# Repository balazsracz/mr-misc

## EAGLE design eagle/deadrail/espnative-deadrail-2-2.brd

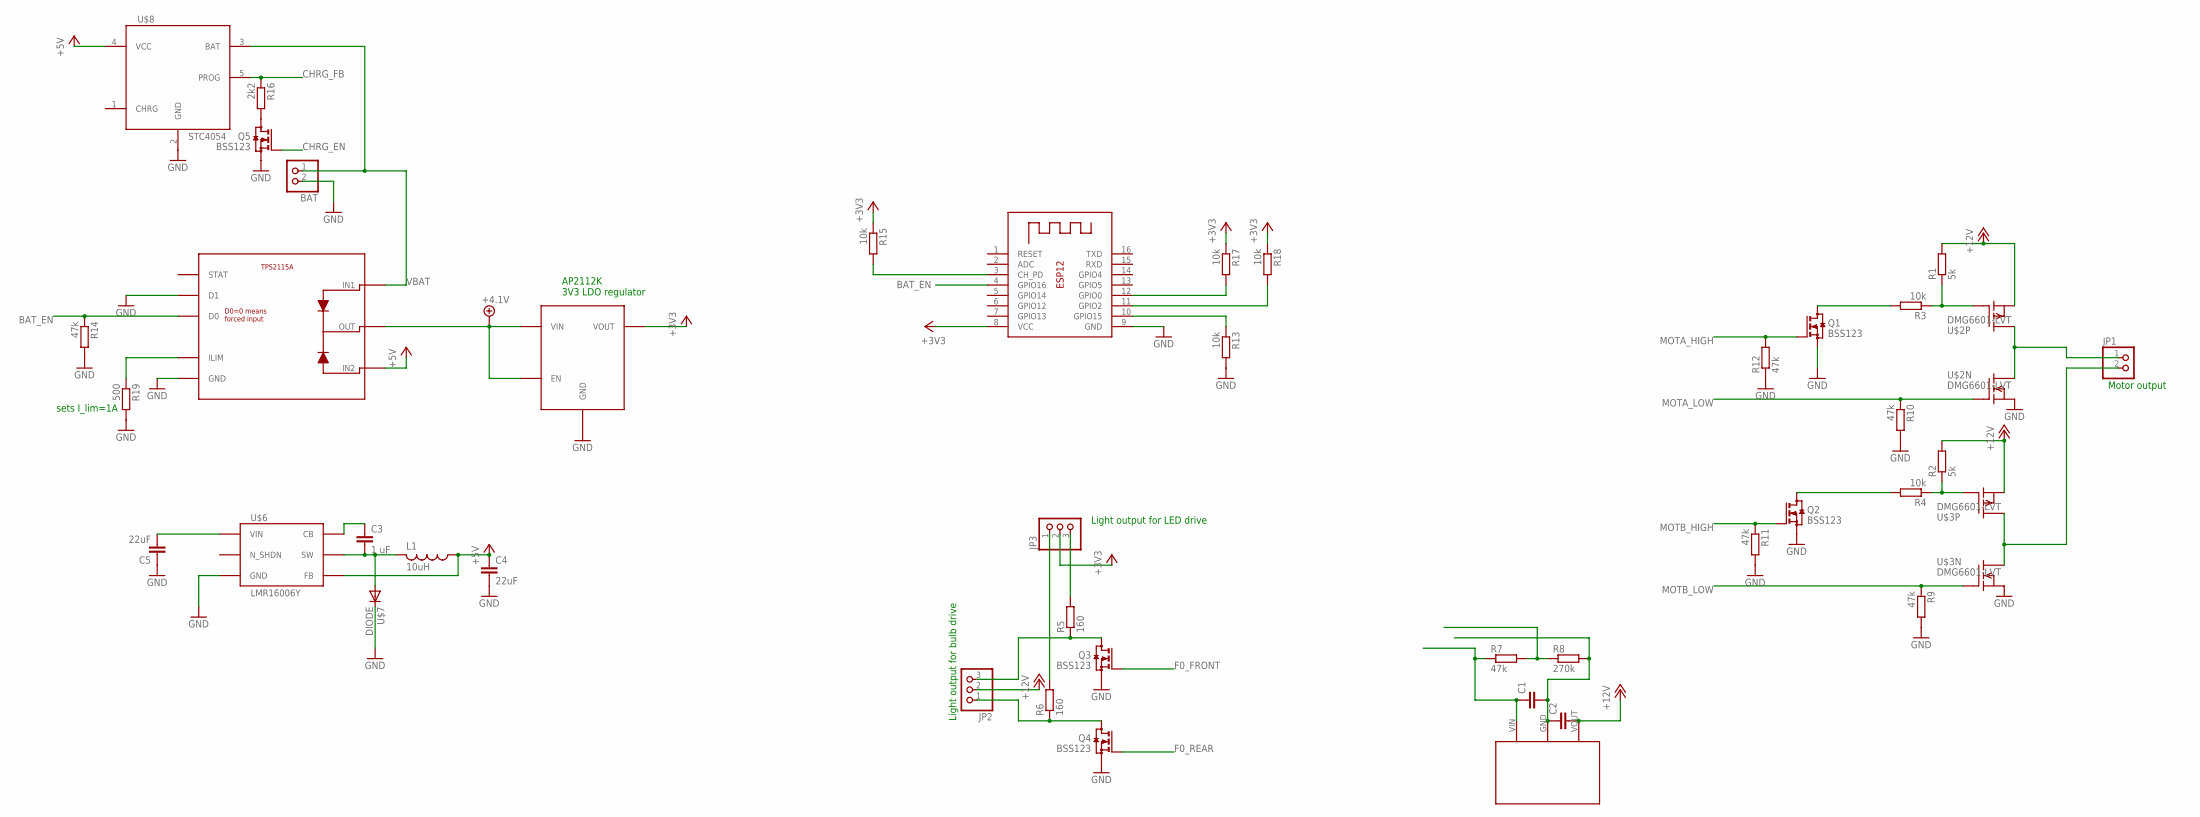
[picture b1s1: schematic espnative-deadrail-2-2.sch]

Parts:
BAT: JST_2PIN-SMT-RA; JST-PH-2-SMT-RA
C1, C2: C-EUC1210; C1210
C3: 1 uF; C0603
C4: 22uF; C0603
C5: 22uF; C1206
JP1: PINHD-1X2; 1X02
JP2, JP3: PINHD-1X3; 1X03
L1: 10uH; FDSD0420
Q1, Q2, Q3, Q4, Q5: BSS123; SOT23
R1, R2: 5k; R0805
R3, R4: 10k; R0805
R5, R6: 160; R0805
R7, R9, R10, R11, R12: 47k; R0805
R8: 270k; R0805
R13, R15, R17, R18: 10k; R0603
R14: 47k; R0603
R16: 2k2; R0603
R19: 500; R0603
U$1: AP2112K-3V3; SOT23-5L
U$2, U$3: DMG6601-LVT; TSOT-26
U$4: TPS2115A; TSSOP-8
U$5: POLOLU-VREG12; POLOLU-REGULATOR
U$6: LMR16006Y; SOT23-6
U$7: DIODE; DIODE-1206
U$8: STC4054; SOT23-5L
X1: ESP-12

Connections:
+3V3: JP3.2, R15.1, R17.1, R18.1, U$1.5 (VOUT), X1.8 (VCC)
+4.1V: U$1.1 (VIN), U$1.3 (EN), U$4.7 (OUT)
+5V: C4.1, L1.P$1 (1), U$4.6 (IN2), U$6.3 (FB), U$8.4 (VCC)
+12V: C2.2, JP2.2, R1.2, R2.2, U$2.2 (S), U$3.2 (S), U$5.VOUT
BAT_EN: R14.1, U$4.2 (D0), X1.4 (GPIO16)
CHRG_EN: Q5.1 (G)
CHRG_FB: R16.1, U$8.5 (PROG)
F0_FRONT: Q3.1 (G)
F0_REAR: Q4.1 (G)
GND: BAT.2 (1), C1.2, C2.1, C4.2, C5.1, Q1.2 (S), Q2.2 (S), Q3.2 (S), Q4.2 (S), Q5.2 (S), R8.2, R9.2, R10.2, R11.2, R12.1, R13.2, R14.2, R19.2, U$1.2 (GND), U$2.5 (S), U$3.5 (S), U$4.3 (D1), U$4.5 (GND), U$5.GND, U$6.2 (GND), U$7.C, U$8.2 (GND), X1.9 (GND)
MOTA_HIGH: Q1.1 (G), R12.2
MOTA_LOW: R10.1, U$2.1 (G)
MOTB_HIGH: Q2.1 (G), R11.1
MOTB_LOW: R9.1, U$3.1 (G)
unnamed: JP1.1, U$2.4 (D), U$2.6 (D)
unnamed: R1.1, R3.1, U$2.3 (G)
unnamed: Q2.3 (D), R4.2
unnamed: R2.1, R4.1, U$3.3 (G)
unnamed: C3.2, L1.P$2 (2), U$6.6 (SW), U$7.A
unnamed: Q1.3 (D), R3.2
unnamed: JP1.2, U$3.4 (D), U$3.6 (D)
unnamed: C3.1, U$6.1 (CB)
unnamed: C5.2, U$6.5 (VIN)
unnamed: Q5.3 (D), R16.2
unnamed: JP2.3, Q3.3 (D), R5.1
unnamed: JP2.1, Q4.3 (D), R6.1
unnamed: JP3.3, R5.2
unnamed: JP3.1, R6.2
unnamed: R15.2, X1.3 (CH_PD)
unnamed: R17.2, X1.12 (GPIO0)
unnamed: R7.2, R8.1
unnamed: R18.2, X1.11 (GPIO2)
unnamed: R13.1, X1.10 (GPIO15)
unnamed: R19.1, U$4.4 (ILIM)
VBAT: BAT.1 (2), C1.1, R7.1, U$4.8 (IN1), U$5.VIN, U$8.3 (BAT)

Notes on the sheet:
Motor output
Light output for LED drive
Light output for bulb drive
AP2112K 3V3 LDO regulator
sets I_lim=1A

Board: 2 copper layers, 43 parts (0 on the bottom side), 32 nets, no tracks yet.
